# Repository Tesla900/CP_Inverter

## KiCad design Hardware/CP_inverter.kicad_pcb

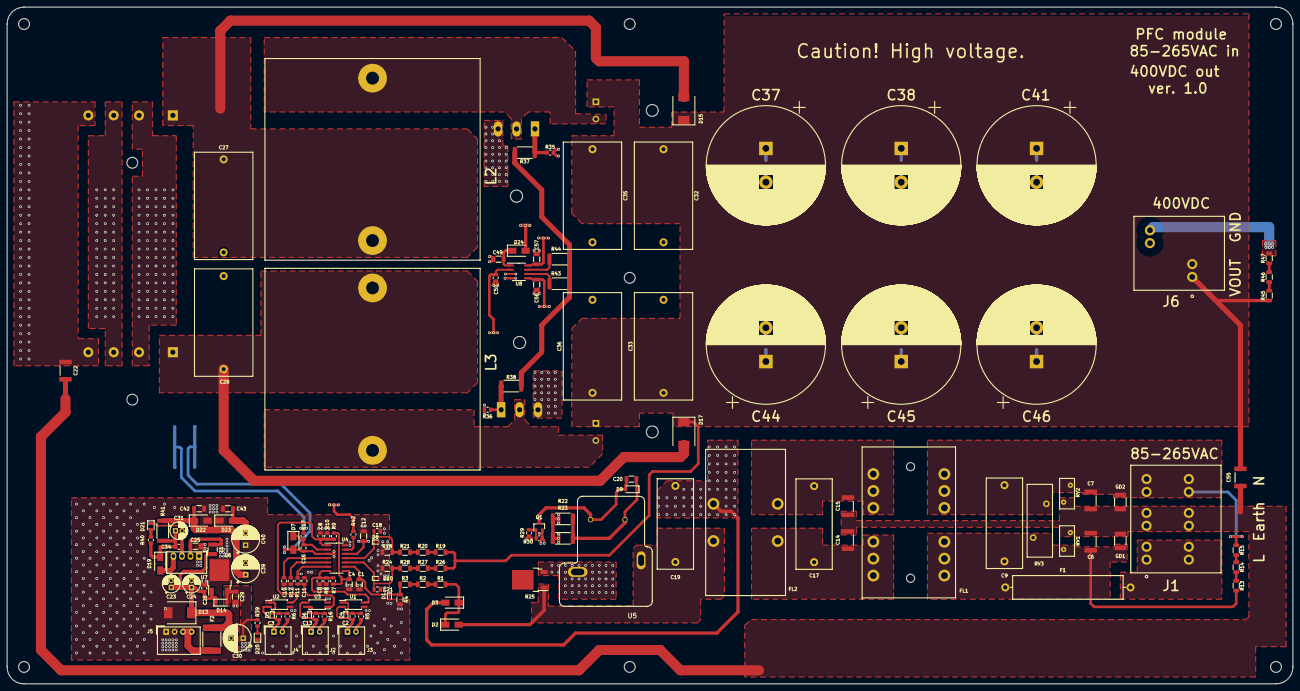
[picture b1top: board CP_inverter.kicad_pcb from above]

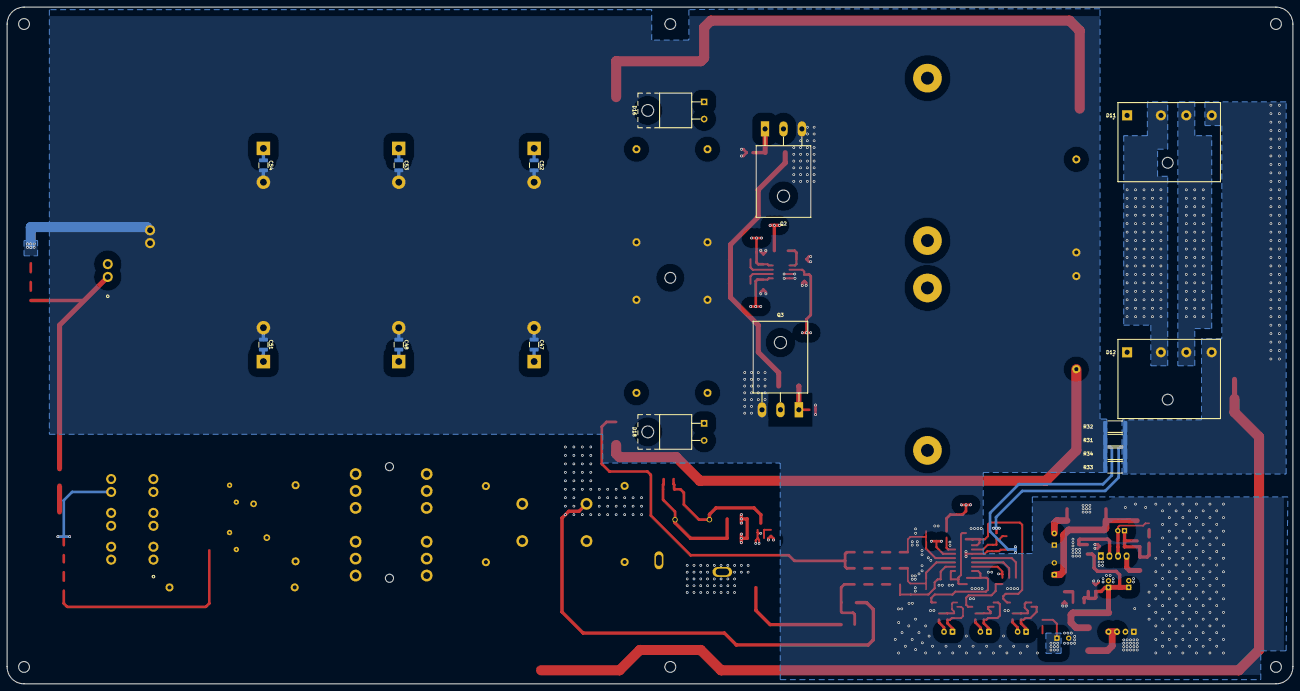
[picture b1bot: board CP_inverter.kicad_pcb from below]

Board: 4 copper layers, 380.0 x 200.0 mm, 164 parts (16 on the bottom side), 68 nets.

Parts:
C1, C4, C12, C20, C25, C29, C42, C43, C49, C56, C57: 10uF; C_1206_3216Metric
C2, C3, C11, C13, C26, C34: 0.1uF; C_0805_2012Metric
C5, C8, C18: 10nF; C_0805_2012Metric
C6, C7, C14, C15: 2.2nF; C_2211_5728Metric
C9, C17, C19: 1.5uF; C_Rect_L26.5mm_W10.5mm_P22.50mm_MKS4
C10, C16: 4.7nF; C_0805_2012Metric
C21, C50: 22pF; C_0805_2012Metric
C22, C55: 1nF; C_2211_5728Metric
C23, C24, C31: 22uF; CP_Radial_D5.0mm_P2.00mm
C27, C28, C32, C33, C35, C36: 1.5uF; C_Rect_L31.5mm_W17.0mm_P27.50mm_MKS4
C30, C39, C40: 330uF; CP_Radial_D8.0mm_P3.50mm
C37, C38, C41, C44, C45, C46: 330uF; CP_Radial_D35.0mm_P10.00mm_SnapIn
C47, C48, C51, C52, C53, C54: 0.1uF; C_1210_3225Metric
D1, D4, D5, D6, D8, D10: PESD5V0L1UB,115; D_SOD-523
D2, D3, D7, D19, D24: MRA4007T3G; D_SMA
D9, D14: 1N5819; D_SOD-123
D11, D12: 50A; CONV_TS50P07GHD2G
D13: SMCJ30A; D_SMC
D15, D17: S15MC V7G; D_SMC
D16, D18: C6D10065A; TO-220-2_Horizontal_TabUp
D20, D21: GREEN; LED_0805_2012Metric
D22: 15V; D_SMA
D23: 5.1V; D_SMA
F1: 50A; Fuse_SunFuse-6HP
F2: 1A; Fuse_2920_7451Metric
FL1: 1.5mH@10kHz; CommonMode_Wuerth_WE-CMBNC
FL2: 500uH@10kHz; CommonMode_Wuerth_WE-CMB-XXL
GD1, GD2: SG500Q; GDT_1812
H1, H2, H3, H4, H5, H6, H7: MountingHole; MountingHole_3.2mm_M3_DIN965
J1: Weidmueller 1988610000; Weidmueller_1988610000
J2, J3, J4: PGood; Molex_SPOX_5268-02A_1x02_P2.50mm_Horizontal
J5: Power in; Molex_SPOX_5268-04A_1x04_P2.50mm_Horizontal
J6: Weidmueller 2453690000; Weidmueller_2453690000
L1: 6.8uH; L_1210_3225Metric
L2, L3: 250uH; D62mm_P32.6mm_x2
Q1: IRLML0030TRPBF; SOT-23
Q2, Q3: C3M0060065D; TO-247-3_Horizontal_TabUp
R1, R2, R3, R13, R14, R15, R19, R20, R21, R26, R27, R28, R45, R46, R47: 1M; R_1206_3216Metric
R4: 47.5K; R_1206_3216Metric
R5, R6, R11, R16, R29: 470R; R_0805_2012Metric
R7, R30, R35, R36, R39, R40: 10K; R_0805_2012Metric
R8: 6.2K; R_0805_2012Metric
R9, R10: 200K; R_0805_2012Metric
R12: 47.5K; R_0805_2012Metric
R17: 68R; R_0805_2012Metric
R18: 18.7K; R_1206_3216Metric
R22, R23: 33R; R_2512_6332Metric
R24: 17.4K; R_1206_3216Metric
R25: 25R; DPAK_Resistor
R31, R32: DNP; R_2512_6332Metric
R33, R34: 0.009R; R_2512_6332Metric
R37, R38, R43, R44: 0.5R; R_2512_6332Metric
R41: 220R; R_2512_6332Metric
R42: 100R; R_0805_2012Metric
RV1, RV2: 820471511; RV_Disc_D9mm_W4.4mm_P5mm
RV3: 820422711; RV_Disc_D21.5mm_W7.5mm_P10mm
U1, U2, U3: LTV-217-C; SO-4_4.4x2.3mm_P1.27mm
U4: ICE3PCS01G; SOIC-14_3.9x8.7mm_P1.27mm
U5: T9VV1K15-12S; RELAY_T9VV1K15-12S
U6: L7815ACD2T; TO-252-2
U7: B2424-1WR2; Converter_DCDC_Murata_MEE1SxxxxSC_THT
U8: UCC5390SCD; SOIC-8_3.9x4.9mm_P1.27mm

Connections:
+15V: C39.1, C42.1, C56.1, D22.1, R41.1, U8.5
-5V: C31.2, C34.2, C40.2, C43.2, C57.2, D21.1, D23.2, U7.3, U8.8
AC_IN1: C19.1, D2.2, FL2.2, R25.1, U5.3
AC_IN2: C19.2, D3.2, D11.3, D12.3, FL2.4
BOFO_ENBL+: J4.2, R6.1
BOFO_ENBL-: C3.2, D5.2, J4.1, U2.2
CS1: C22.1, D11.4, D12.4, R17.2, R31.1, R32.1, R33.1, R34.1
DRIVER_IN+: R42.1, U4.13
Earth: C6.2, C7.1, C14.2, C15.1, C22.2, C55.2, GD1.1, GD2.3, J1.2, RV1.2, RV2.1
GATE: R37.2, R38.2, R43.2, R44.2
GND: C1.2, C4.2, C5.2, C8.2, C10.2, C11.2, C12.1, C16.1, C18.2, C21.2, C23.2, C24.2, C25.2, C26.2, C27.2, C28.2, C29.2, C30.2, C32.2, C33.2, C35.2, C36.2, C37.2, C38.2, C39.2, C40.1, C41.2, C42.2, C43.1, C44.2, C45.2, C46.2, C47.2, C48.2, C49.2, C50.2, C51.2, C52.2, C53.2, C54.2, C56.2, C57.1, D1.2, D7.2, D8.2, D10.2, D13.2, D20.1, D22.2, D23.1, J5.1, J5.2, J6.2, Q1.2, Q2.3, Q3.3, R4.1, R8.1, R10.1, R12.1, R18.1, R24.1, R30.1, R31.2, R32.2, R33.2, R34.2, R35.2, R36.2, R47.2, U1.3, U2.3, U3.2, U4.3, U4.14, U6.2, U7.1, U8.3, U8.4
unnamed: C1.1, D1.1, R3.1, R4.2, U4.9
unnamed: C2.1, D4.1, R5.2, U1.1
unnamed: C3.1, D5.1, R6.2, U2.1
unnamed: C4.1, R7.2, R9.2, U4.8
unnamed: C5.1, R7.1, R8.2, U1.4, U4.7
unnamed: C6.1, C9.1, F1.2, FL1.1, GD1.3, R13.2, RV1.1, RV3.1
unnamed: C7.2, C9.2, FL1.3, GD2.1, J1.3, R15.1, RV2.2, RV3.2
unnamed: C8.1, R9.1, R10.2, U2.4, U4.1
unnamed: C10.1, U4.4
unnamed: C11.1, R11.1, U3.1
unnamed: C13.1, D6.1, R16.2, U3.4
unnamed: C14.1, C17.1, FL1.2, FL2.1
unnamed: C15.2, C17.2, FL1.4, FL2.3
unnamed: C16.2, D7.1, R17.1, U4.2
unnamed: C18.1, D8.1, R18.2, R21.1, U4.11
unnamed: C20.1, D9.1, R22.1, R23.1, U5.2
unnamed: C20.2, D9.2, Q1.3, U5.1
unnamed: C21.1, D10.1, R24.2, R28.1, U4.10
unnamed: C23.1, C24.1, C26.1, D13.1, D14.1, F2.1, L1.1, U6.1
unnamed: C25.1, L1.2, U7.2
unnamed: C27.1, D11.1, D15.2, L2.1
unnamed: C28.1, D12.1, D17.2, L3.1
unnamed: C31.1, C34.1, D19.1, R40.2, R41.2
unnamed: C49.1, D24.1, U8.1
unnamed: C50.1, R42.2, U8.2
unnamed: D2.1, D3.1, R1.2
unnamed: D11.2, D12.2, R25.2, U5.4
unnamed: D16.2, L2.2, Q2.2
unnamed: D18.2, L3.2, Q3.2
unnamed: D19.2, U7.4
unnamed: D20.2, R39.1
unnamed: D21.2, R40.1
unnamed: F1.1, J1.1
unnamed: F2.2, J5.3, J5.4
unnamed: Q1.1, R29.2, R30.2
unnamed: Q2.1, R35.1, R37.1
unnamed: Q3.1, R36.1, R38.1
unnamed: R1.1, R2.2
unnamed: R2.1, R3.2
unnamed: R12.2, U4.5
unnamed: R13.1, R14.2
unnamed: R14.1, R15.2
unnamed: R19.1, R20.2
unnamed: R20.1, R21.2
unnamed: R26.1, R27.2
unnamed: R27.1, R28.2
unnamed: R43.1, U8.6
unnamed: R44.1, U8.7
unnamed: R45.2, R46.1
unnamed: R46.2, R47.1
PFC_ENBL+: J3.2, R5.1
PFC_ENBL-: C2.2, D4.2, J3.1, U1.2
PGOOD_SIGNAL+: J2.2, R16.1
PGOOD_SIGNAL-: C13.2, D6.2, J2.1, U3.3
VBUS: C32.1, C33.1, C35.1, C36.1, C37.1, C38.1, C41.1, C44.1, C45.1, C46.1, C47.1, C48.1, C51.1, C52.1, C53.1, C54.1, C55.1, D15.1, D16.1, D17.1, D18.1, J6.1, R19.2, R26.2, R45.1
VB_OK: R11.2, R29.1, U4.6
VCC: C12.2, C29.1, C30.1, D14.2, D24.2, R22.2, R23.2, R39.2, U4.12, U6.3

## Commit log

2021-01-17 new: Schematic ready
2021-01-21 new: Rev. 1.0 common phases
2021-01-22 new: Rev. 1.0 common phases finish
2021-01-24 new: Work in progress
2021-01-28 new: Work in progress, filter layout
2021-02-01 new: first rev
2021-02-02 new: rev. 1.0. fixes
2021-02-02 new: production files added
2021-02-27 new: PSFB files added
2021-03-02 new: PSFB PCB progress
2021-03-08 new: PSFB PCB rev. 1.0
2021-03-11 new: PSFB PCB rev. 1.0 hotfix
